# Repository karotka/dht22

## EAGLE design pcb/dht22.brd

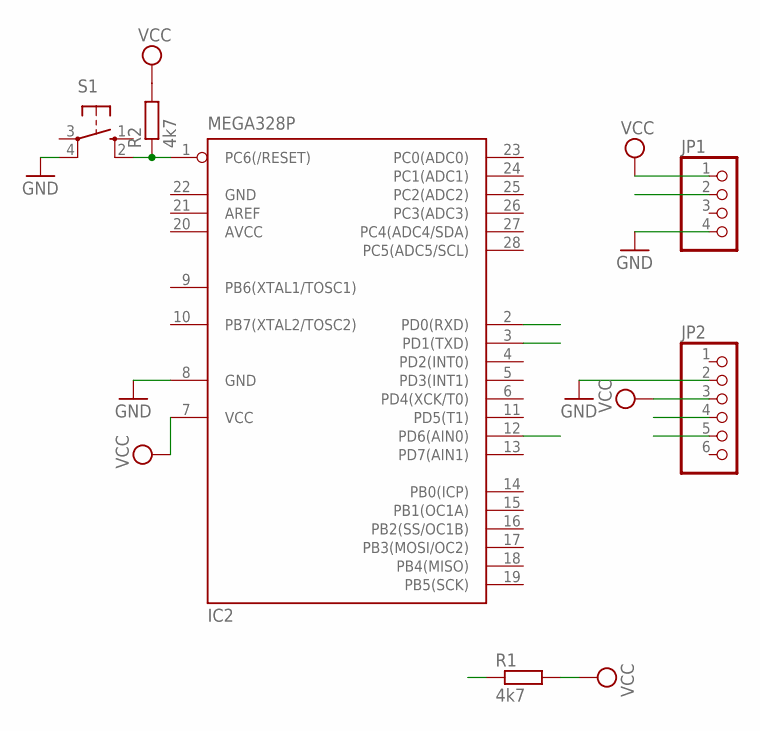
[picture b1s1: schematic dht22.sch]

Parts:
IC2: MEGA328P; DIL28-3
JP1: PINHD-1X4; 1X04
JP2: PINHD-1X6; 1X06
R1, R2: 4k7; 0207/10
S1: 10-XX; B3F-10XX

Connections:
AVCC: IC2.20 (AVCC)
GND: IC2.8 (GND), IC2.22 (GND), JP1.4, JP2.2, S1.4 (P1)
unnamed: IC2.1 (PC6(/RESET)), R2.1, S1.2 (S1)
PD6: IC2.12 (PD6(AIN0)), JP1.2, R1.1
RX: IC2.2 (PD0(RXD)), JP2.4
TX: IC2.3 (PD1(TXD)), JP2.5
VCC: IC2.7 (VCC), JP1.1, JP2.3, R1.2, R2.2

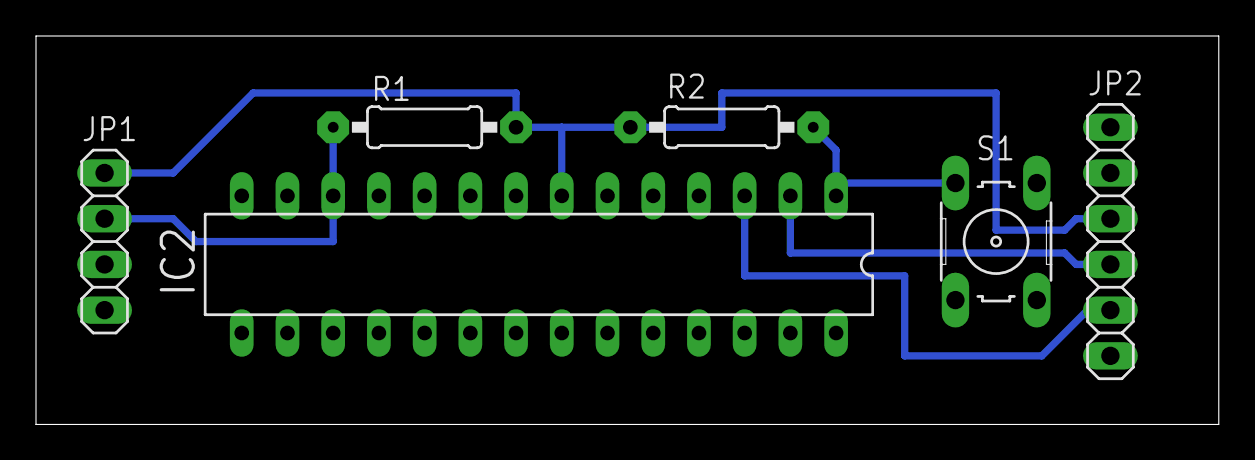
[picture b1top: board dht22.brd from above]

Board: 2 copper layers, 65.7 x 21.6 mm, 6 parts (0 on the bottom side), 6 nets.

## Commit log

2015-01-27 add all
2015-01-30 add web
